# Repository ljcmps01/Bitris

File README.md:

# Bitris
Proyecto de instalaciones industriales
Se trata de un juego el cual consta de controlar los leds de una matriz con un boton, la matriz desplazará un bit de izquierda a derecha 
en la fila superior, el jugador tendrá un boton que al presionarlo dejará caer el bit al fondo de la matriz.
El objetivo del juego es que el jugador llene todas las filas de la matriz pero siempre una fila a la vez; si el jugador comienza a apilar
La siguiente fila sin haber completado la que se encuentra, perderá una vida, a medida que vaya llenando las filas el juego se volverá mas
veloz.

## Changelog:

_28-03 Funcionamiento de la matriz (delay)_

_10-04 Control de la matriz (Habilitacion de que leds prender)_

_11-04 Funcionamiento de la matriz (TIMER)_

_12-04 Multiplexado de la matriz (Prescaler a 1024 con OCR1A=3,5,8)_

_12-04 Control de velocidad de niveles y desplazamiento del jugador_

_12-04 Deteccion del boton del jugador y animacion de caida (velocidad constante)_

_13-04 1er ensamble: Multiplexado+Desplazamiento+boton+caida_

_13-04 Se agrega la capacidad de mantener el led prendido en el fondo tras realizar la animacion de caida_

_13-04 Se le agrega control de vida y nivel (La vida es solo visual y no afecta el juego todavia)_

_17/04 Se creó programa con animaciones basicas, horizontales y verticales_

_17/04 El boton da inicio al primer juego, se agregó animación cuando se pierde y reinicio con el boton_

~~**[Arreglar falso inicio]**~~

_22/04 VerticalClean, HorizontalClean, Blink pasadas a TIMER_

_23/04 animacion de FillUp pasada a TIMER_

_23/04 Renovacion de Bitris con animaciones de inicio, perdida y victoria (En timer), Falso inicio arreglado_

_23/04 Definiciones Globales del juego_

---------------**FIN DEL CUERPO PRINCIPAL**----------------

_24/04 Creado programa de Display de vida y nivel con CD4511_

_24/04 Acoplado el control de displays al programa principal_

_30/07 Realizado programa para Arduino UNO_

_30/07 Realizado PCB de placa principal_

_13/08 Realizado PCB de placa displays_

_16/08 Adjuntado informe del proyecto_

_19/08 Agregado Diseño 3D del gabinete_

_03/09 Arreglo de diseño de PCB principal_

_12/09 Diseño 3D de la rampa de las monedas_

_20/09 Diseño 3D de la matriz LED_

_08/10 Diseño 3D divididos en partes del gabinete_

_08/10 Conclusion de codigo Bitris Pago_

_05/11 Se agregó la musica principal del juego_

_06/11 Se realizaron pruebas en protoboard con el parlante para un decente sonido_

_08/11 Se realizó el esquematico del amplificador_

_11/11 Arreglado problemas de la musica_

_11/11 Realizado programa de pago CON MUSICA_

## Bugs/Trabajo por hacer:

### Software 

* **LED fantasma**

* **Doble pulsacion**

* Agregar sonido (Principal hecho, falta perdida de vidas, punto, nivel, fin ganado, gameover)

### Hardware 

* Diseñar amplificador (PCB)

* Montar placas (Resta amplificador)

## Creadores

Alejo Rodrigo Campos (@ljcmps01):

* -_Primer programa de control Arduino MEGA_-

* -_Primer diseño SCH y PCB_-

* -_Modelos en 3D_-

Alex Obregon (@alobre4148):

* -_Programa compatible Arduino UNO_ (Programa a utilizar para producto final)-

* -_Diseño PCB final placa principal_-

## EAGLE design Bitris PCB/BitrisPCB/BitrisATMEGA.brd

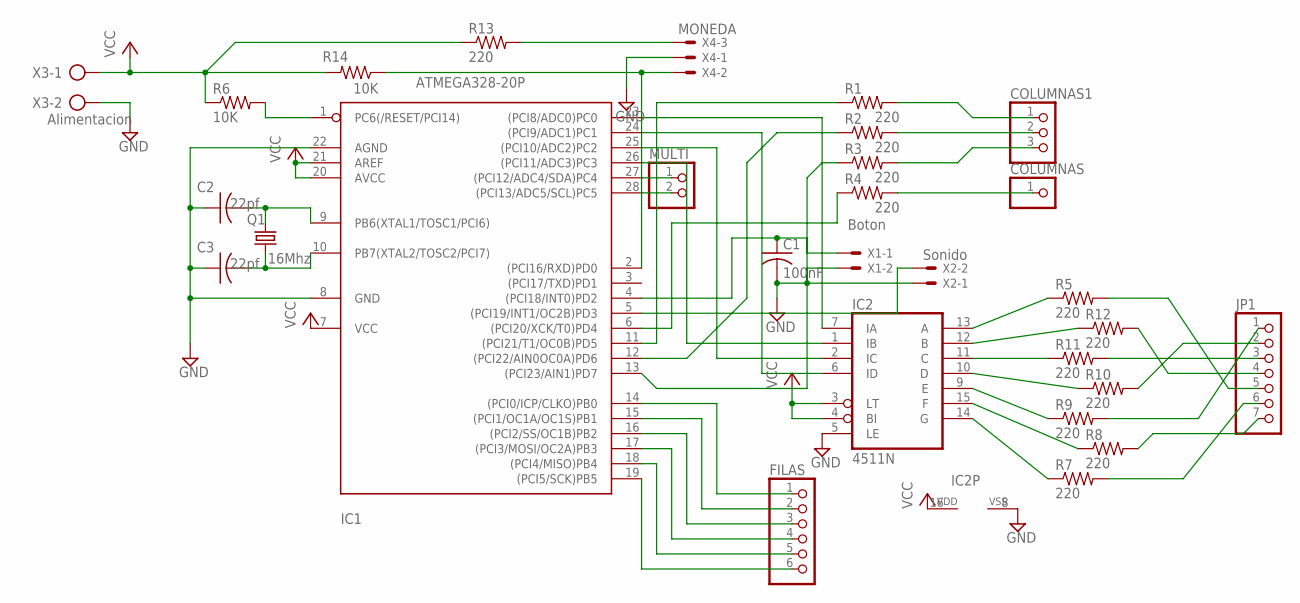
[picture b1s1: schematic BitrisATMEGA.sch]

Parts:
C1: 100nF; C0805
C2, C3: 22pf; C0805
COLUMNAS: PINHD-1X1; 1X01
COLUMNAS1: PINHD-1X3; 1X03
FILAS: PINHD-1X6; 1X06
IC1: ATMEGA328-20P; DIL28-3
IC2: 4511N; DIL16
JP1: PINHD-1X7; 1X07
MULTI: PINHD-1X2; 1X02
Q1: 16Mhz; HC49/S
R1, R2, R3, R5, R7, R8, R9, R10, R11, R12, R13: 220; M0805
R4: 220; 0204/5
R6, R14: 10K; M0805
X1: Boton; 22-23-2021
X2: Sonido; 22-23-2021
X3: Alimentacion; AK500/2
X4: MONEDA; 22-23-2031

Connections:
GND: C1.2, C2.1, C3.1, IC1.8 (GND), IC1.22 (AGND), IC2.5 (LE), IC2.8 (VSS), X1.2, X2.1, X3.2, X4.1
unnamed: COLUMNAS1.1, R1.2
unnamed: COLUMNAS1.2, R2.2
unnamed: COLUMNAS1.3, R3.2
unnamed: COLUMNAS.1, R4.2
unnamed: IC1.23 ((PCI8/ADC0)PC0), IC2.7 (IA)
unnamed: IC1.24 ((PCI9/ADC1)PC1), IC2.6 (ID)
unnamed: IC1.25 ((PCI10/ADC2)PC2), IC2.2 (IC)
unnamed: IC1.26 ((PCI11/ADC3)PC3), IC2.1 (IB)
unnamed: FILAS.1, IC1.14 ((PCI0/ICP/CLKO)PB0)
unnamed: FILAS.2, IC1.15 ((PCI1/OC1A/OC1S)PB1)
unnamed: FILAS.3, IC1.16 ((PCI2/SS/OC1B)PB2)
unnamed: FILAS.4, IC1.17 ((PCI3/MOSI/OC2A)PB3)
unnamed: FILAS.5, IC1.18 ((PCI4/MISO)PB4)
unnamed: FILAS.6, IC1.19 ((PCI5/SCK)PB5)
unnamed: IC1.27 ((PCI12/ADC4/SDA)PC4), MULTI.1
unnamed: IC1.28 ((PCI13/ADC5/SCL)PC5), MULTI.2
unnamed: IC1.6 ((PCI20/XCK/T0)PD4), R4.1
unnamed: IC1.11 ((PCI21/T1/OC0B)PD5), R1.1
unnamed: C2.2, IC1.9 (PB6(XTAL1/TOSC1/PCI6)), Q1.2
unnamed: C3.2, IC1.10 (PB7(XTAL2/TOSC2/PCI7)), Q1.1
unnamed: IC1.13 ((PCI23/AIN1)PD7), R3.1
unnamed: IC2.10 (D), R10.1
unnamed: IC2.11 (C), R11.1
unnamed: IC2.12 (B), R12.1
unnamed: IC2.13 (A), R5.1
unnamed: IC2.9 (E), R9.1
unnamed: IC2.15 (F), R8.1
unnamed: IC2.14 (G), R7.1
unnamed: IC1.2 ((PCI16/RXD)PD0), R14.1, X4.2
unnamed: IC1.5 ((PCI19/INT1/OC2B)PD3), X2.2
unnamed: C1.1, IC1.4 ((PCI18/INT0)PD2), X1.1
unnamed: IC1.1 (PC6(/RESET/PCI14)), R6.2
unnamed: JP1.1, R9.2
unnamed: JP1.2, R10.2
unnamed: JP1.3, R11.2
unnamed: JP1.4, R12.2
unnamed: JP1.5, R5.2
unnamed: JP1.6, R7.2
unnamed: JP1.7, R8.2
unnamed: R13.2, X4.3
unnamed: IC1.12 ((PCI22/AIN0OC0A)PD6), R2.1
VCC: IC1.7 (VCC), IC1.20 (AVCC), IC1.21 (AREF), IC2.3 (LT), IC2.4 (BI), IC2.16 (VDD), R6.1, R13.1, R14.2, X3.1

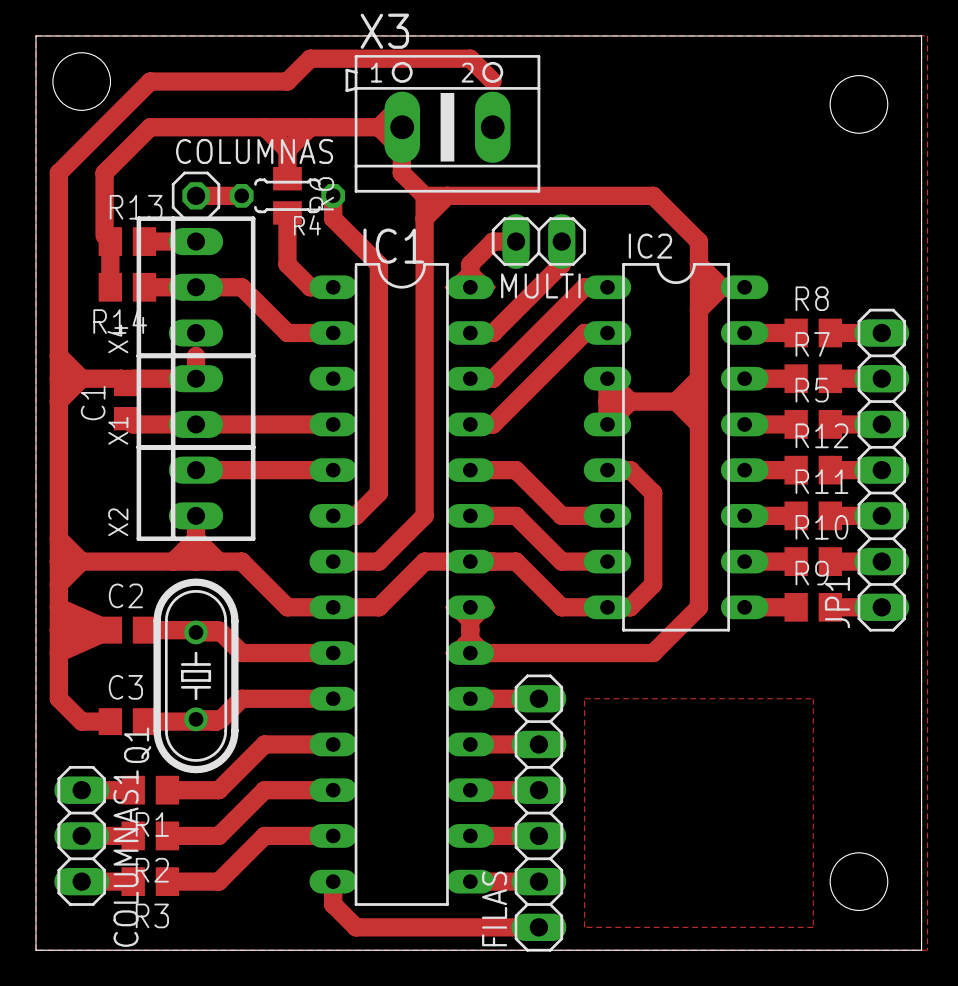
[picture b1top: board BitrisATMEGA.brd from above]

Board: 2 copper layers, 49.2 x 50.8 mm, 29 parts (0 on the bottom side), 43 nets.

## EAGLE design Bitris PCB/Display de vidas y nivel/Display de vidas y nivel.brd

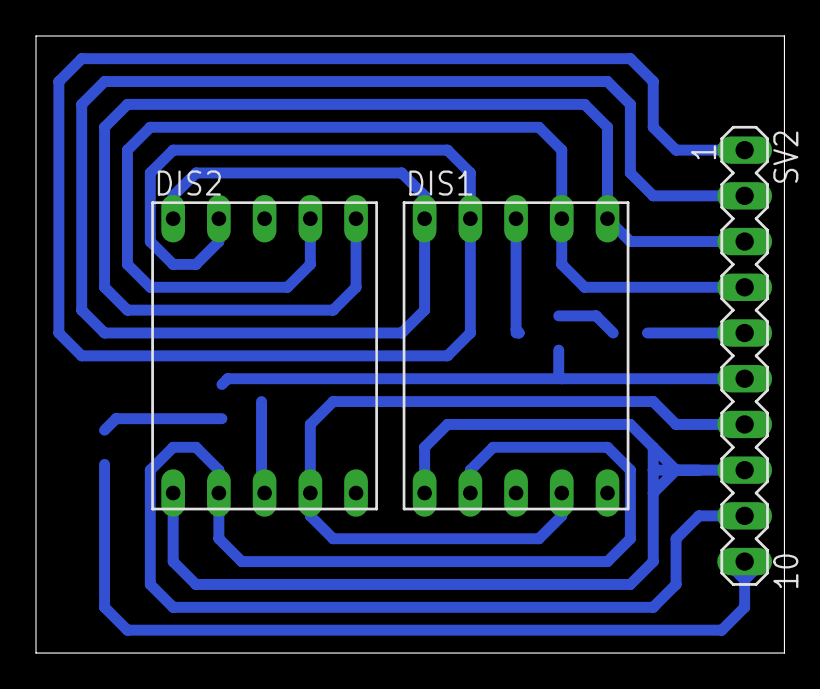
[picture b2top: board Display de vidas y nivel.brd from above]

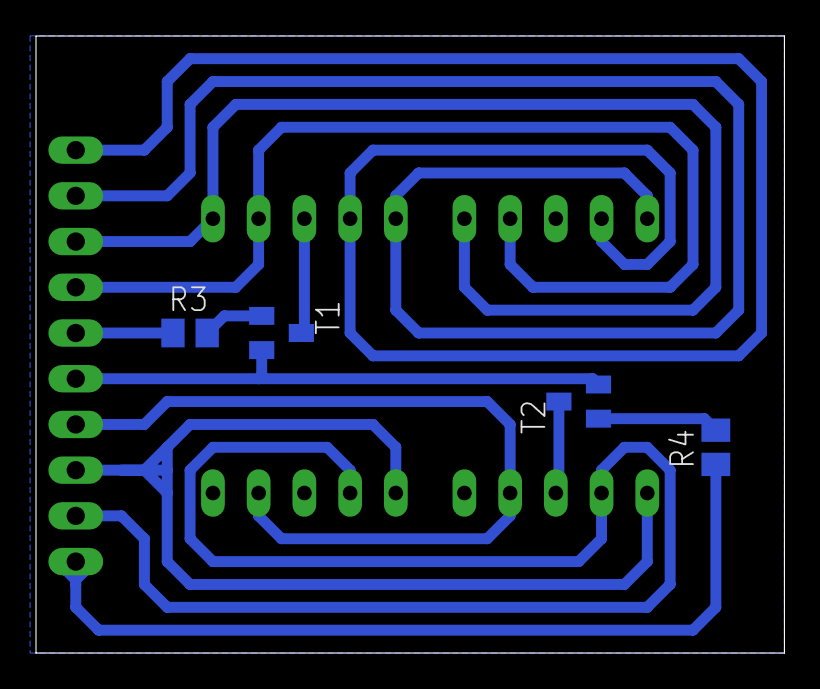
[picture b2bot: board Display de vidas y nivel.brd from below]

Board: 2 copper layers, 41.6 x 34.3 mm, 7 parts (4 on the bottom side), 14 nets.

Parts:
DIS1, DIS2: HD-H101; HDSP-M
R3, R4: M0805
SV2: MA10-1
T1, T2: BC848; SOT23

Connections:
GND: SV2.6, T1.2, T2.2
unnamed: R3.2, T1.1
unnamed: DIS1.6, DIS2.6, SV2.3
unnamed: DIS1.4, DIS2.4, SV2.7
unnamed: DIS1.2, DIS2.2, SV2.9
unnamed: DIS1.1, DIS2.1, SV2.8
unnamed: DIS1.9, DIS2.9, SV2.1
unnamed: DIS1.10, DIS2.10, SV2.2
unnamed: DIS1.3, DIS1.8, T1.3
unnamed: DIS2.3, DIS2.8, T2.3
unnamed: R3.1, SV2.5
unnamed: R4.2, T2.1
unnamed: DIS1.7, DIS2.7, SV2.4
unnamed: R4.1, SV2.10

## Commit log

2019-03-27 Base de programa controlador de la matriz
2019-04-14 Programa de multiplexado de la matriz
2019-04-14 Prueba para implementar GitHub
2019-04-15 Descripcion del proyecto y changelog
2019-04-15 Programa de control de boton de jugador y animacion de caida
2019-04-15 Determinado velocidades segun nivel
2019-04-15 Agregada la capacidad de apilar bits con el boton
2019-04-15 Programa de compatibidad entre desplazamiento de usuario y multiplexado de la pantalla
2019-04-15 Programas varios que en conjunto llevaron al primer ensamble del programa final
2019-04-15 Programa principal del juego, ensamble funcional sin limite de juego
2019-04-17 Agregue Inicio y reinicio con boton y animaciones basicas
2019-04-17 Programa con las funciones de animacion del juego
2019-04-17 Actualizado el changelog
2019-04-21 Agregadas mas funciones para el juego
2019-04-22 Comentarios en las variables del juego
2019-04-22 Pasadas animaciones de barrido y parpadeo a TIMER
2019-04-22 Changelog update
2019-04-23 Pasada funcion restante a TIMER
2019-04-23 Agregadas animaciones de inicio, derrota y victoria, Correccion de falso inicio
2019-04-24 Agregadas declaraciones globales al juego para mejor y mas simple configuracion del juego
2019-04-24 Programa de display de vidas y niveles
2019-04-24 Acoplado del control de display con el programa principal
2019-05-31 Arreglada compatibilidad en cambio de macros
2019-06-04 Mejorada compatibilidad con diversas cantidades de filas y columnas
2019-08-16 bitrisUNO
2019-08-16 Git ignore agregado
2019-08-16 Actualizacion de README
2019-08-16 PCBprincipal
2019-08-16 datos agregados
2019-08-17 Agregado informe y circuitos de displays
2019-08-18 Agregado archivo DWG del modelo 3D del gabinete del Bitrix
2019-08-20 Actualizacion del repositorio y agregado diseño 3D del gabinete
2019-08-20 Actualizacion del informe
2019-08-21 PCB modificado
2019-09-17 PCB 2.0
2019-09-17 Readme nuevo
2019-09-23 Modelos 3D del juego: Matriz y rampa de monedas
2019-10-09 Añadido archivos varios de diferentes piezas del gabinete para guia de tamaños y diseño e impresion 3D
2019-10-09 Update del Readme
2019-10-10 Agrego de codigo Bitris Pago
2019-10-10 Acutualizacion Readme
2019-10-24 Update menor del PCB de Displays
2019-10-24 Update menor
2019-11-08 Añadidos ficheros y datos de la musica de fondo
2019-11-08 Agregado esquematico de la mini placa del Parlante
2019-11-08 Actualizado README
2019-11-10 Añadido diagrama de flujo y fix menor de la musica
2019-11-10 Limpieza del diseño principal
2019-11-11 Agregado Informe Final del proyecto
2019-11-11 modificado informe viejo por memoria tecnica
2019-11-11 Ajuste SCH
2019-11-11 Arreglado problemas de musica y programa pago
2019-11-12 PCB DISPLAYs
2019-11-12 Actualizado informe
